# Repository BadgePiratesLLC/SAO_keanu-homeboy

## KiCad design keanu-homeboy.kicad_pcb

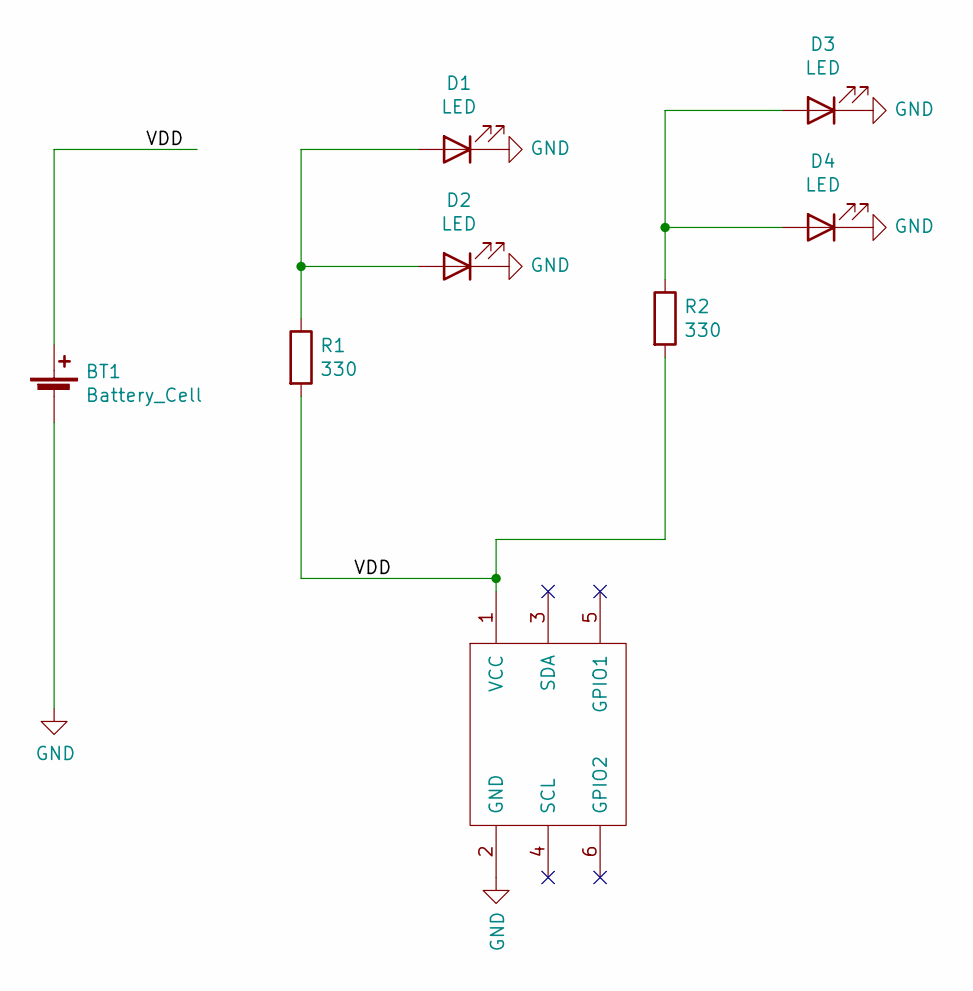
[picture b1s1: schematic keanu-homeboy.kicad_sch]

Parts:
BT1: Battery_Cell; BatteryHolder_MPD_BC2003_1x2032
D1, D2, D3, D4: LED; QBLP615
R1, R2: 330; R_0805_2012Metric_Pad1.20x1.40mm_HandSolder
X1: Badgelife_sao_connector_v169bis; Badgelife-SAOv169-SAO_Side_B.SLK; MPN 0878340619

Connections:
/VDD: BT1.1 (+), R1.2, R2.2, X1.1 (VCC)
GND: BT1.2 (-), D1.1 (K), D2.1 (K), D3.1 (K), D4.1 (K), X1.2 (GND)
unnamed: D1.2 (A), D2.2 (A), R1.1
unnamed: D3.2 (A), D4.2 (A), R2.1

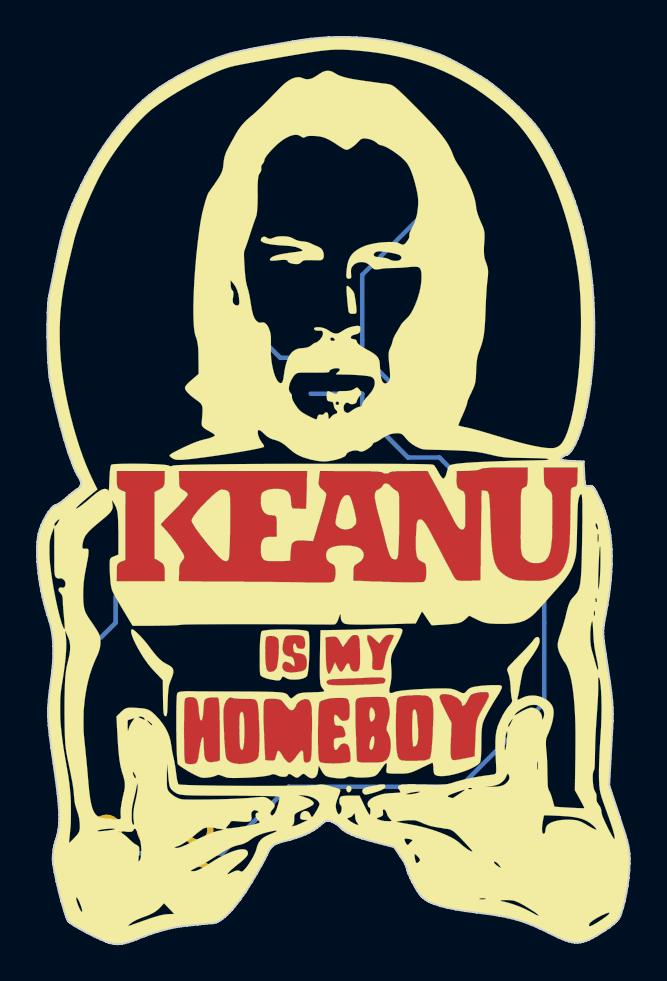
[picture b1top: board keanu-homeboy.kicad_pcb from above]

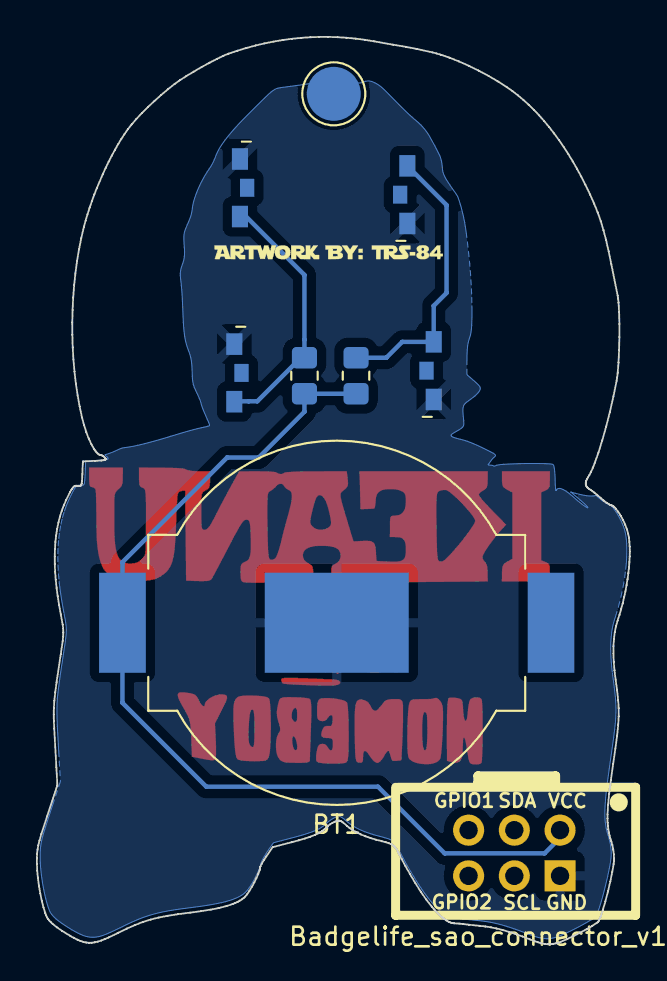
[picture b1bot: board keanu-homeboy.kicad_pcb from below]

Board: 2 copper layers, 32.9 x 50.4 mm, 8 parts (7 on the bottom side), 4 nets.

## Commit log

2019-07-03 keanu
2019-07-12 final keanu
2019-09-14 added pin version
2019-09-14 forgot zipped gerbers
2024-07-21 Update kicad version
2024-07-22 updates for production
2024-07-22 Fixed ground plane issue and updated schematic to KiCad8
2024-07-22 Added production files for panel
2024-07-22 Added panel step file
2024-07-31 updates and stuff
